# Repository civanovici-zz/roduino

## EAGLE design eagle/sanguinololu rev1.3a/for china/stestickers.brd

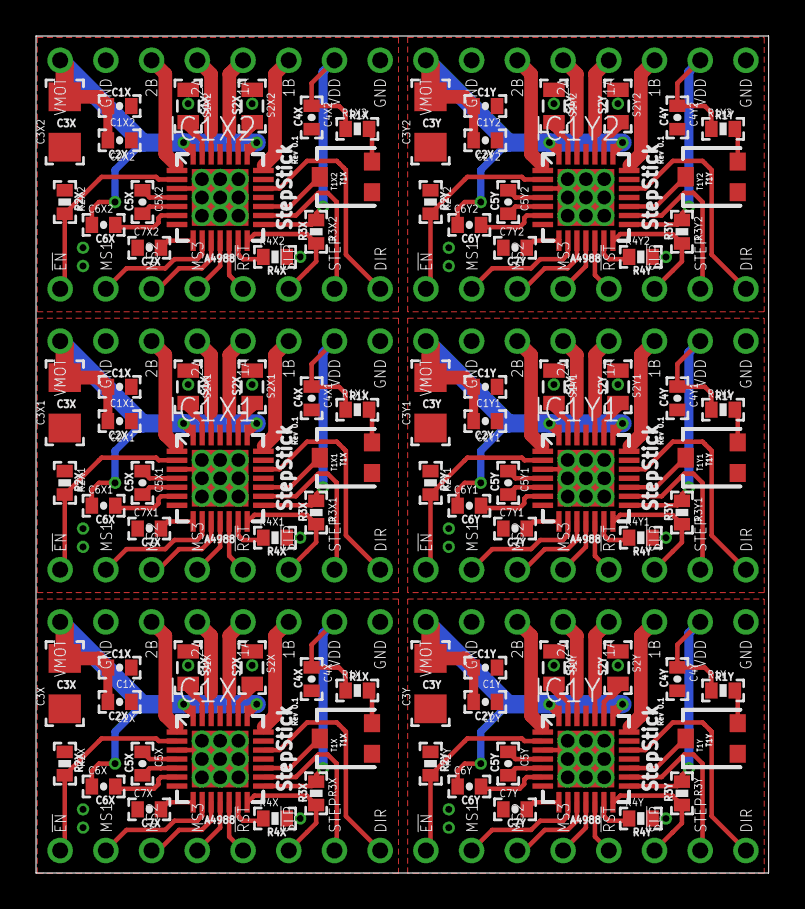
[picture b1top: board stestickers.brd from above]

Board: 2 copper layers, 40.7 x 46.5 mm, 96 parts (0 on the bottom side), 135 nets.

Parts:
C1X, C1X1, C1X2, C1Y, C1Y1, C1Y2, C2X, C2X1, C2X2, C2Y, C2Y1, C2Y2, C5X, C5X1, C5X2, C5Y, C5Y1, C5Y2, C6X, C6X1, C6X2, C6Y, C6Y1, C6Y2: .1uf; 0402-CAP
C3X, C3X1, C3X2, C3Y, C3Y1, C3Y2: 4.7uF; 1206
C4X, C4X1, C4X2, C4Y, C4Y1, C4Y2, C7X, C7X1, C7X2, C7Y, C7Y1, C7Y2: .22uf; 0402-CAP
IC1X, IC1X1, IC1X2, IC1Y, IC1Y1, IC1Y2: A4988; QFN28ET
J1X, J1X1, J1X2, J1Y, J1Y1, J1Y2: CLONOLU
R1X, R1X1, R1X2, R1Y, R1Y1, R1Y2: 20k; 0402-RES
R2X, R2X1, R2X2, R2Y, R2Y1, R2Y2, R3X, R3X1, R3X2, R3Y, R3Y1, R3Y2: 100k; 0402-RES
R4X, R4X1, R4X2, R4Y, R4Y1, R4Y2: 10k; 0402-RES
S1X, S1X1, S1X2, S1Y, S1Y1, S1Y2, S2X, S2X1, S2X2, S2Y, S2Y1, S2Y2: 0.2; 0805
T1X, T1X1, T1X2, T1Y, T1Y1, T1Y2: TRIM; TRIMPOT-3MM

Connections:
GND: C1X.1, C1Y.1, C2X.1, C2Y.1, C3X.1, C3Y.1, C4X.2, C4Y.2, C7X.1, C7Y.1, IC1X.3, IC1X.7, IC1X.18, IC1X.20, IC1X.25, IC1X.EXP, IC1Y.3, IC1Y.7, IC1Y.18, IC1Y.20, IC1Y.25, IC1Y.EXP, J1X.GND$1, J1X.GND$2, J1Y.GND$1, J1Y.GND$2, R2X.1, R2Y.1, R4X.2, R4Y.2, S1X.1, S1Y.1, S2X.1, S2Y.1, T1X.1, T1Y.1
GND1: C1X1.1, C1Y1.1, C2X1.1, C2Y1.1, C3X1.1, C3Y1.1, C4X1.2, C4Y1.2, C7X1.1, C7Y1.1, IC1X1.3, IC1X1.7, IC1X1.18, IC1X1.20, IC1X1.25, IC1X1.EXP, IC1Y1.3, IC1Y1.7, IC1Y1.18, IC1Y1.20, IC1Y1.25, IC1Y1.EXP, J1X1.GND$1, J1X1.GND$2, J1Y1.GND$1, J1Y1.GND$2, R2X1.1, R2Y1.1, R4X1.2, R4Y1.2, S1X1.1, S1Y1.1, S2X1.1, S2Y1.1, T1X1.1, T1Y1.1
GND2: C1X2.1, C1Y2.1, C2X2.1, C2Y2.1, C3X2.1, C3Y2.1, C4X2.2, C4Y2.2, C7X2.1, C7Y2.1, IC1X2.3, IC1X2.7, IC1X2.18, IC1X2.20, IC1X2.25, IC1X2.EXP, IC1Y2.3, IC1Y2.7, IC1Y2.18, IC1Y2.20, IC1Y2.25, IC1Y2.EXP, J1X2.GND$1, J1X2.GND$2, J1Y2.GND$1, J1Y2.GND$2, R2X2.1, R2Y2.1, R4X2.2, R4Y2.2, S1X2.1, S1Y2.1, S2X2.1, S2Y2.1, T1X2.1, T1Y2.1
VDD: C4X.1, C4Y.1, IC1X.15, IC1Y.15, J1X.VDD, J1Y.VDD, R1X.1, R1Y.1, R3X.1, R3Y.1
VDD1: C4X1.1, C4Y1.1, IC1X1.15, IC1Y1.15, J1X1.VDD, J1Y1.VDD, R1X1.1, R1Y1.1, R3X1.1, R3Y1.1
VDD2: C4X2.1, C4Y2.1, IC1X2.15, IC1Y2.15, J1X2.VDD, J1Y2.VDD, R1X2.1, R1Y2.1, R3X2.1, R3Y2.1
VMOT: C1X.2, C1Y.2, C2X.2, C2Y.2, C3X.2, C3Y.2, C6X.1, C6Y.1, IC1X.22, IC1X.28, IC1Y.22, IC1Y.28, J1X.VMOT, J1Y.VMOT
VMOT1: C1X1.2, C1Y1.2, C2X1.2, C2Y1.2, C3X1.2, C3Y1.2, C6X1.1, C6Y1.1, IC1X1.22, IC1X1.28, IC1Y1.22, IC1Y1.28, J1X1.VMOT, J1Y1.VMOT
VMOT2: C1X2.2, C1Y2.2, C2X2.2, C2Y2.2, C3X2.2, C3Y2.2, C6X2.1, C6Y2.1, IC1X2.22, IC1X2.28, IC1Y2.22, IC1Y2.28, J1X2.VMOT, J1Y2.VMOT
XCP1: C5X.1, IC1X.4
XCP2: C5X.2, IC1X.5
XCP3: C5X1.1, IC1X1.4
XCP4: C5X1.2, IC1X1.5
XCP5: C5X2.1, IC1X2.4
XCP6: C5X2.2, IC1X2.5
XDIR: IC1X.19, J1X.DIR
XDIR1: IC1X1.19, J1X1.DIR
XDIR2: IC1X2.19, J1X2.DIR
XENABLE: IC1X.2, J1X.!EN, R2X.2
XENABLE1: IC1X1.2, J1X1.!EN, R2X1.2
XENABLE2: IC1X2.2, J1X2.!EN, R2X2.2
XMS1: IC1X.9, J1X.MS1
XMS2: IC1X.10, J1X.MS2
XMS3: IC1X.11, J1X.MS3
XMS4: IC1X1.9, J1X1.MS1
XMS5: IC1X1.10, J1X1.MS2
XMS6: IC1X1.11, J1X1.MS3
XMS7: IC1X2.9, J1X2.MS1
XMS8: IC1X2.10, J1X2.MS2
XMS9: IC1X2.11, J1X2.MS3
XOUT1A: IC1X.24, J1X.1A
XOUT1A1: IC1X1.24, J1X1.1A
XOUT1A2: IC1X2.24, J1X2.1A
XOUT1B: IC1X.21, J1X.1B
XOUT1B1: IC1X1.21, J1X1.1B
XOUT1B2: IC1X2.21, J1X2.1B
XOUT2A: IC1X.26, J1X.2A
XOUT2A1: IC1X1.26, J1X1.2A
XOUT2A2: IC1X2.26, J1X2.2A
XOUT2B: IC1X.1, J1X.2B
XOUT2B1: IC1Y.1, J1Y.2B
XOUT2B2: IC1X1.1, J1X1.2B
XOUT2B3: IC1Y1.1, J1Y1.2B
XOUT2B4: IC1X2.1, J1X2.2B
XOUT2B5: IC1Y2.1, J1Y2.2B
XREF: IC1X.17, T1X.2
XREF1: IC1X1.17, T1X1.2
XREF2: R1X.2, T1X.3
XREF3: R1X1.2, T1X1.3
XREF4: IC1X2.17, T1X2.2
XREF5: R1X2.2, T1X2.3
XRESET: IC1X.12, J1X.!RST
XRESET1: IC1X1.12, J1X1.!RST
XRESET2: IC1X2.12, J1X2.!RST
XROSC: IC1X.13, R4X.1
XROSC1: IC1X1.13, R4X1.1
XROSC2: IC1X2.13, R4X2.1
XSENSE1: IC1X.23, S2X.2
XSENSE2: IC1X.27, S1X.2
XSENSE3: IC1X1.27, S1X1.2
XSENSE4: IC1X1.23, S2X1.2
XSENSE5: IC1X2.27, S1X2.2
XSENSE6: IC1X2.23, S2X2.2
XSLEEP: IC1X.14, J1X.!SLP, R3X.2
XSLEEP1: IC1X1.14, J1X1.!SLP, R3X1.2
XSLEEP2: IC1X2.14, J1X2.!SLP, R3X2.2
XSTEP: IC1X.16, J1X.STEP
XSTEP1: IC1X1.16, J1X1.STEP
XSTEP2: IC1X2.16, J1X2.STEP
XVCP: C6X.2, IC1X.6
XVCP1: C6X1.2, IC1X1.6
XVCP2: C6X2.2, IC1X2.6
XVREG: C7X.2, IC1X.8
XVREG1: C7X1.2, IC1X1.8
XVREG2: C7X2.2, IC1X2.8
YCP1: C5Y.1, IC1Y.4
YCP2: C5Y.2, IC1Y.5
YCP3: C5Y1.1, IC1Y1.4
YCP4: C5Y1.2, IC1Y1.5
YCP5: C5Y2.1, IC1Y2.4
YCP6: C5Y2.2, IC1Y2.5
YDIR1: IC1Y.19, J1Y.DIR
YDIR2: IC1Y1.19, J1Y1.DIR
YDIR3: IC1Y2.19, J1Y2.DIR
YENABLE: IC1Y.2, J1Y.!EN, R2Y.2
YENABLE1: IC1Y1.2, J1Y1.!EN, R2Y1.2
YENABLE2: IC1Y2.2, J1Y2.!EN, R2Y2.2
YMS1: IC1Y.9, J1Y.MS1
YMS2: IC1Y.10, J1Y.MS2
YMS3: IC1Y.11, J1Y.MS3
YMS4: IC1Y1.9, J1Y1.MS1
YMS5: IC1Y1.10, J1Y1.MS2
YMS6: IC1Y1.11, J1Y1.MS3
YMS7: IC1Y2.9, J1Y2.MS1
YMS8: IC1Y2.10, J1Y2.MS2
YMS9: IC1Y2.11, J1Y2.MS3
YOUT1A: IC1Y.24, J1Y.1A
YOUT1A1: IC1Y1.24, J1Y1.1A
YOUT1A2: IC1Y2.24, J1Y2.1A
YOUT1B: IC1Y.21, J1Y.1B
YOUT1B1: IC1Y1.21, J1Y1.1B
YOUT1B2: IC1Y2.21, J1Y2.1B
YOUT2A: IC1Y.26, J1Y.2A
YOUT2A1: IC1Y1.26, J1Y1.2A
YOUT2A2: IC1Y2.26, J1Y2.2A
YREF: IC1Y.17, T1Y.2
YREF1: R1Y.2, T1Y.3
YREF2: IC1Y1.17, T1Y1.2
YREF3: R1Y1.2, T1Y1.3
YREF4: IC1Y2.17, T1Y2.2
YREF5: R1Y2.2, T1Y2.3
YRESET: IC1Y.12, J1Y.!RST
YRESET1: IC1Y1.12, J1Y1.!RST
YRESET2: IC1Y2.12, J1Y2.!RST
YROSC: IC1Y.13, R4Y.1
YROSC1: IC1Y1.13, R4Y1.1
YROSC2: IC1Y2.13, R4Y2.1
YSENSE1: IC1Y.23, S2Y.2
YSENSE2: IC1Y.27, S1Y.2
YSENSE3: IC1Y1.27, S1Y1.2
YSENSE4: IC1Y1.23, S2Y1.2
YSENSE5: IC1Y2.27, S1Y2.2
YSENSE6: IC1Y2.23, S2Y2.2
YSLEEP: IC1Y.14, J1Y.!SLP, R3Y.2
YSLEEP1: IC1Y1.14, J1Y1.!SLP, R3Y1.2
YSLEEP2: IC1Y2.14, J1Y2.!SLP, R3Y2.2
YSTEP: IC1Y.16, J1Y.STEP
YSTEP1: IC1Y1.16, J1Y1.STEP
YSTEP2: IC1Y2.16, J1Y2.STEP
YVCP: C6Y.2, IC1Y.6
YVCP1: C6Y1.2, IC1Y1.6
YVCP2: C6Y2.2, IC1Y2.6
YVREG: C7Y.2, IC1Y.8
YVREG1: C7Y1.2, IC1Y1.8
YVREG2: C7Y2.2, IC1Y2.8

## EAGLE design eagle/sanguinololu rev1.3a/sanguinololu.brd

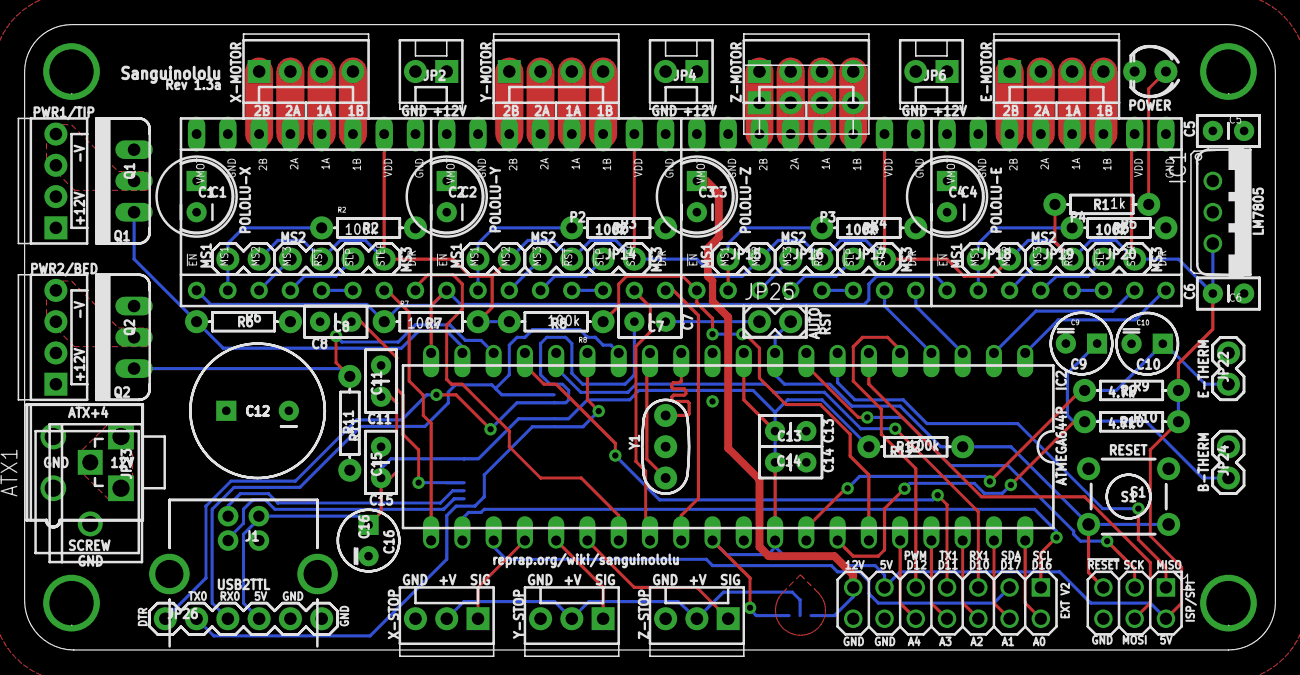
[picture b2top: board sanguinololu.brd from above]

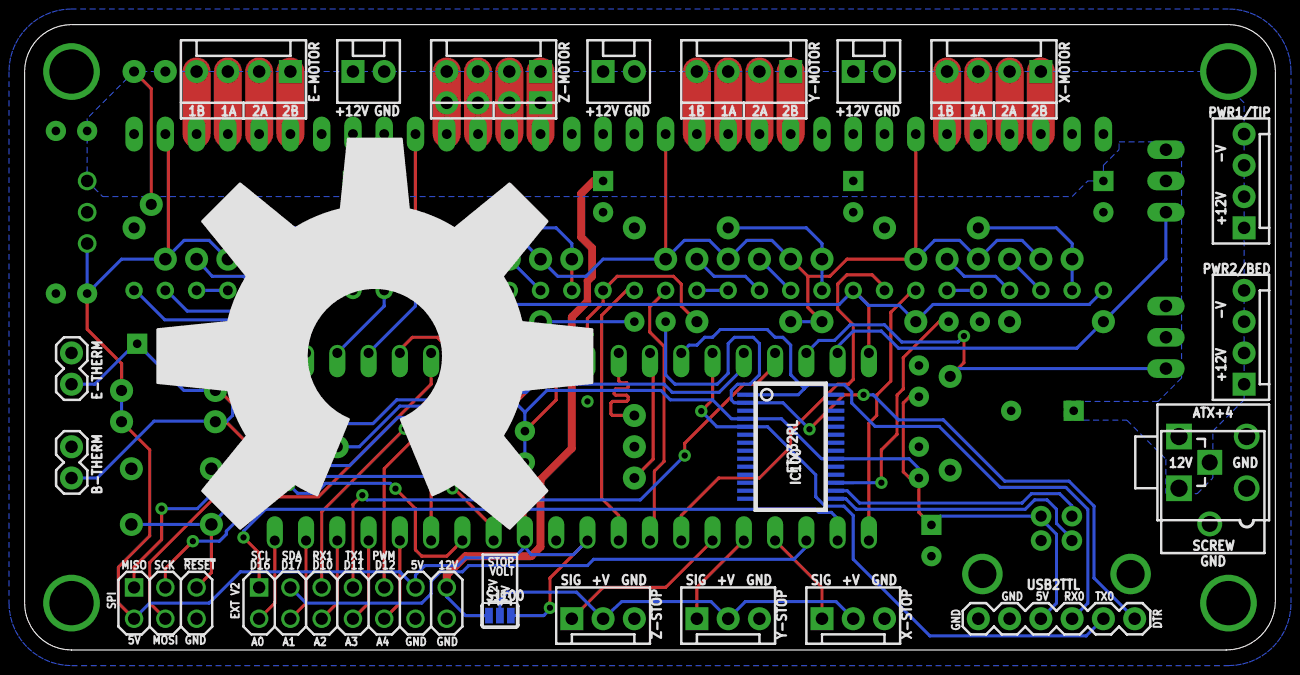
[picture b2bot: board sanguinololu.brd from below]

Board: 2 copper layers, 101.6 x 50.8 mm, 77 parts (2 on the bottom side), 79 nets.

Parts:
ATX1: ATX-4VERTICAL; MINIFITJR-4-VERTICAL
C1, C2, C3, C4: 100uf; CPOL-RADIAL-100UF-25V
C5: 0.33uF; CAP-PTH-SMALL2
C6, C7, C8, C11, C13, C14, C15: 0.1uF; CAP-PTH-SMALL2
C9, C10: 10uF; CPOL-RADIAL-10UF-25V
C12: 1000uF; CPOL-RADIAL-1000UF-25V
C16: 4.7uF; CPOL-RADIAL-10UF-25V
IC1: LM7805; 78XXL-CUSTOM
IC2: ATMEGA644-20PU; DIL40
IC100: FT232RL; SSOP28DB
J1: USB; USB-B-PTH
JP1: MOT-X; MOLEX-1X4
JP2, JP4, JP6: 12VPWR; MOLEX-1X2
JP3: MOT-Y; MOLEX-1X4
JP5, JP30: MOT-Z; MOLEX-1X4
JP7: MOT-E; MOLEX-1X4
JP8: HOTEND; MOLEX-1X4
JP9: X-MS1; 1X02
JP10: X-MS2; 1X02
JP11: X-MS3; 1X02
JP12: Y-MS1; 1X02
JP13: Y-MS2; 1X02
JP14: Y-MS3; 1X02
JP15: Z-MS1; 1X02
JP16: Z-MS2; 1X02
JP17: Z-MS3; 1X02
JP18: E-MS1; 1X02
JP19: E-MS2; 1X02
JP20: E-MS3; 1X02
JP21: HOTBED; MOLEX-1X4
JP22: E-THERM; 1X02
JP23: SCREW; SCREWTERMINAL-5MM-2
JP24: B-THERM; 1X02
JP25: AUTO RESET; 1X02
JP26: USB2TTL; 1X06
JP27: X-STOP; MOLEX-1X3
JP28: Y-STOP; MOLEX-1X3
JP29: Z-STOP; MOLEX-1X3
LED1: POWER; LED3MM
P1: POLOLU-X; POLOLU-ALLEGRO-PTH
P2: POLOLU-Y; POLOLU-ALLEGRO-PTH
P3: POLOLU-Z; POLOLU-ALLEGRO-PTH
P4: POLOLU-E; POLOLU-ALLEGRO-PTH
Q1, Q2: RFP30N06LE; TO220V
R1: 1k; AXIAL-0.3
R2, R3, R4, R5, R7, R8, R12: 100k; AXIAL-0.3
R6, R11: 10k; AXIAL-0.3
R9, R10: 4.7k; AXIAL-0.3
S1: RESET; TACTILE-PTH
SJ100: 5v/12v; SJ_3
U$17, U$37, U$38: PLATED-SCREW; PLATEDSCREW
U$24: IO_HEADERS_SCREW; IO_HEADER-PLATEDSCREW
Y1: 16MHz 22pF; RESONATOR-PTH

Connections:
3V3: C8.1, IC100.17
5V: C6.1, C11.1, C13.2, C14.1, C15.1, C16.1, IC1.OUT, IC2.10, IC2.30, IC2.32, IC100.4, IC100.20, J1.VBUS, JP9.2, JP10.2, JP11.2, JP12.2, JP13.2, JP14.2, JP15.2, JP16.2, JP17.2, JP18.2, JP19.2, JP20.2, JP26.4, P1.VDD, P2.VDD, P3.VDD, P4.VDD, R1.P$2, R7.P$2, R8.P$2, R9.P$2, R10.P$2, R12.P$2, SJ100.3, U$24.5V, U$24.5V1
12V: ATX1.3, ATX1.4, C1.1, C2.1, C3.1, C4.1, C5.1, C12.1, IC1.IN, JP2.1, JP4.1, JP6.1, JP8.1, JP8.2, JP21.1, JP21.2, JP23.1, P1.VMOT, P2.VMOT, P3.VMOT, P4.VMOT, SJ100.1, U$24.12V
!FTDI-RESET: C7.1, JP25.1
!HOTBED: IC2.18, Q2.1, R11.P$1
!HOTEND: IC2.19, Q1.1, R6.P$1
!RESET: IC2.9, JP25.2, R12.P$1, S1.3, S1.4, U$24.RST
!STEP-ENABLE: IC2.20, P1.!EN, P2.!EN, P4.!EN, R7.P$1
!STEP-ENABLE-Z: IC2.35, P3.!EN, R8.P$1
#DTR: C7.2, IC100.2, JP26.1
A0: IC2.40, U$24.A0
A1: IC2.39, U$24.A1
A2: IC2.38, U$24.A2
A3: IC2.37, U$24.A3
A4: IC2.36, U$24.A4
AIFO: IC2.14, IC100.1, JP26.3
AOFI: IC2.15, IC100.5, JP26.2
B-THERM: C9.1, IC2.34, JP24.1, R10.P$1
E-DIR: IC2.1, P4.DIR
E-MOT-1A: JP7.3, P4.1A
E-MOT-1B: JP7.4, P4.1B
E-MOT-2A: JP7.2, P4.2A
E-MOT-2B: JP7.1, P4.2B
E-MS1: JP18.1, P4.MS1, R5.P$1
E-MS2: JP19.1, P4.MS2
E-MS3: JP20.1, P4.MS3
E-RESETSLEEP: P4.!RST, P4.!SLP
E-STEP: IC2.2, P4.STEP
E-THERM: C10.1, IC2.33, JP22.1, R9.P$1
ENDSTOP+V: JP27.2, JP28.2, JP29.2, SJ100.2
GND: ATX1.1, ATX1.2, C1.2, C2.2, C3.2, C4.2, C5.2, C6.2, C8.2, C9.2, C10.2, C11.2, C12.2, C13.1, C14.2, C15.2, C16.2, IC1.GND, IC2.11, IC2.31, IC100.7, IC100.18, IC100.21, IC100.25, IC100.26, J1.GND, J1.P$1, J1.P$2, JP2.2, JP4.2, JP6.2, JP22.2, JP23.2, JP24.2, JP26.5, JP26.6, JP27.3, JP28.3, JP29.3, LED1.K, P1.GNDMOT, P1.GNDVDD, P2.GNDMOT, P2.GNDVDD, P3.GNDMOT, P3.GNDVDD, P4.GNDMOT, P4.GNDVDD, Q1.3, Q2.3, R2.P$2, R3.P$2, R4.P$2, R5.P$2, R6.P$2, R11.P$2, S1.1, S1.2, U$17.GND, U$24.GND, U$24.GND1, U$24.GND2, U$24.GNDSCREW, U$37.GND, U$38.GND, Y1.2
HOTBED-GND: JP21.3, JP21.4, Q2.2
HOTEND-GND: JP8.3, JP8.4, Q1.2
LED1: LED1.A, R1.P$1
PB4-PWM: IC2.5, U$24.PWM
PB5-MOSI: IC2.6, U$24.MOSI
PB6-MISO: IC2.7, U$24.MISO
PB7-SCK: IC2.8, U$24.SCK
PC0-SCL: IC2.22, U$24.SCL
PC1-SDA: IC2.23, U$24.SDA
PD2-RX1: IC2.16, U$24.RX1
PD3-TX1: IC2.17, U$24.TX1
USBDM: IC100.16, J1.D-
USBDP: IC100.15, J1.D+
X-DIR: IC2.27, P1.DIR
X-MOT-1A: JP1.3, P1.1A
X-MOT-1B: JP1.4, P1.1B
X-MOT-2A: JP1.2, P1.2A
X-MOT-2B: JP1.1, P1.2B
X-MS1: JP9.1, P1.MS1, R2.P$1
X-MS2: JP10.1, P1.MS2
X-MS3: JP11.1, P1.MS3
X-RESETSLEEP: P1.!RST, P1.!SLP
X-STEP: IC2.21, P1.STEP
X-STOP: IC2.24, JP27.1
XTAL1: IC2.13, Y1.3
XTAL2: IC2.12, Y1.1
Y-DIR: IC2.29, P2.DIR
Y-MOT-1A: JP3.3, P2.1A
Y-MOT-1B: JP3.4, P2.1B
Y-MOT-2A: JP3.2, P2.2A
Y-MOT-2B: JP3.1, P2.2B
Y-MS1: JP12.1, P2.MS1, R3.P$1
Y-MS2: JP13.1, P2.MS2
Y-MS3: JP14.1, P2.MS3
Y-RESETSLEEP: P2.!RST, P2.!SLP
Y-STEP: IC2.28, P2.STEP
Y-STOP: IC2.25, JP28.1
Z-DIR: IC2.3, P3.DIR
Z-MOT-1A: JP5.3, JP30.3, P3.1A
Z-MOT-1B: JP5.4, JP30.4, P3.1B
Z-MOT-2A: JP5.2, JP30.2, P3.2A
Z-MOT-2B: JP5.1, JP30.1, P3.2B
Z-MS1: JP15.1, P3.MS1, R4.P$1
Z-MS2: JP16.1, P3.MS2
Z-MS3: JP17.1, P3.MS3
Z-RESETSLEEP: P3.!RST, P3.!SLP
Z-STEP: IC2.4, P3.STEP
Z-STOP: IC2.26, JP29.1

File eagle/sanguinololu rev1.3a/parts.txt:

-----------FTDI-----------,
C7,       0.1uF,            CAPPTH2                   CAP-PTH-SMALL2         
C8,       0.1uF,            CAPPTH2                   CAP-PTH-SMALL2         
C11,      0.1uF,            CAPPTH2                   CAP-PTH-SMALL2         
C15,      0.1uF,            CAPPTH2                   CAP-PTH-SMALL2         
C16,      4.7uF,            CAP_POLPTH2               CPOL-RADIAL-10UF-25V   
IC100,    FT232RL,          FT232RLSSOP               SSOP28DB               
J1,       USB,              USBPTH                    USB-B-PTH              


-----------VREG-----------,
IC1,       LM7805,          VREG-NOGND                VREG-NOGND             vreg
C5,       0.33uF,           CAPPTH2                   CAP-PTH-SMALL2         
C6,       0.1uF,            CAPPTH2                   CAP-PTH-SMALL2         
JP23,     SCREW,            M025MM                    SCREWTERMINAL-5MM-2    


-----------ATX------------,
ATX1,     ATX-4VERTICAL,    ATX-4VERTICAL             MINIFITJR-4-VERTICAL   atx-power-supply
HDDPWR,   5v/12v,           DRIVEPWRVERTICAL          HDD-VERTICAL           atx-power-supply


-----------CORE-----------,
IC2,      ATMEGA644-20PU,   ATMEGA644-20PU            DIL40                  atmel
DIP-40,   SOCKET,
SHUNT,    MS, QTY12
MALE PIN,  QTY70 (10x7)
FEMALE PIN HEADER, 16pin, qty4


LED1,     POWER,            LED3MM                    LED3MM                 
Y1,       16MHz 22pF,       RESONATORPTH              RESONATOR-PTH          
S1,       RESET,            TAC_SWITCHPTH             TACTILE-PTH            
Q1,       RFP30N06LE,       MOSFET-NCHANNELPTH2       TO220V                 
Q2,       RFP30N06LE,       MOSFET-NCHANNELPTH2       TO220V                 

C1,       100uf,            CAP_POLPTH1               CPOL-RADIAL-100UF-35V  
C2,       100uf,            CAP_POLPTH1               CPOL-RADIAL-100UF-35V  
C3,       100uf,            CAP_POLPTH1               CPOL-RADIAL-100UF-35V  
C4,       100uf,            CAP_POLPTH1               CPOL-RADIAL-100UF-35V  
C9,       10uF,             CAP_POLPTH2               CPOL-RADIAL-10UF-35V   
C10,      10uF,             CAP_POLPTH2               CPOL-RADIAL-10UF-35V   
C12,      1000uF,           CAP_POLPTH4               CPOL-RADIAL-1000UF-35V 
C14,      0.1uF,            CAPPTH2                   CAP-PTH-SMALL2         
C13,      0.1uF,            CAPPTH2                   CAP-PTH-SMALL2         

R1,       1k,               RESISTORPTH1              AXIAL-0.3              
R2,       100k,             RESISTORPTH1              AXIAL-0.3              
R3,       100k,             RESISTORPTH1              AXIAL-0.3              
R4,       100k,             RESISTORPTH1              AXIAL-0.3              
R5,       100k,             RESISTORPTH1              AXIAL-0.3              
R6,       10k,              RESISTORPTH1              AXIAL-0.3              
R7,       100k,             RESISTORPTH1              AXIAL-0.3              
R8,       100k,             RESISTORPTH1              AXIAL-0.3              
R9,       4.7k,             RESISTORPTH1              AXIAL-0.3              
R10,      4.7k,             RESISTORPTH1              AXIAL-0.3              
R11,      10k,              RESISTORPTH1              AXIAL-0.3              
R12,      100k,             RESISTORPTH1              AXIAL-0.3

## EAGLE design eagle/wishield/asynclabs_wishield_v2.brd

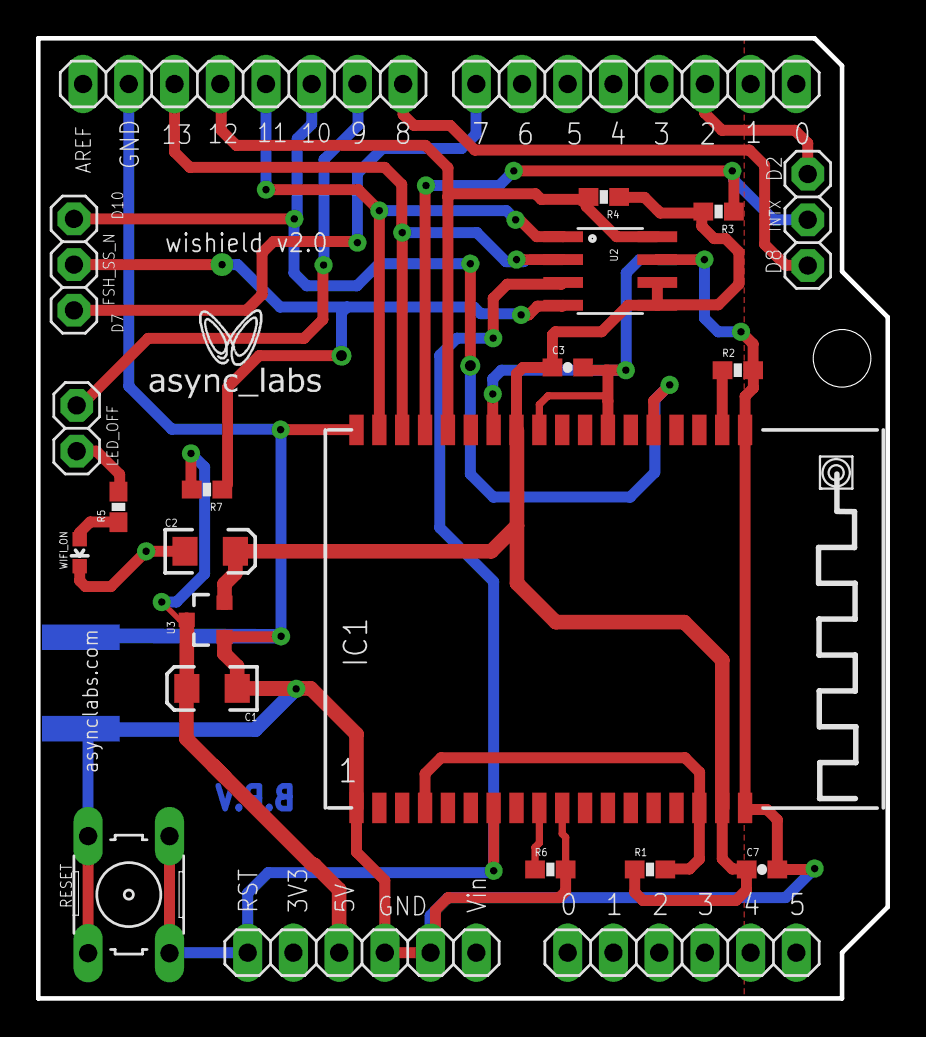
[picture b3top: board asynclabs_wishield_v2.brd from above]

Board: 2 copper layers, 47.2 x 53.3 mm, 23 parts (0 on the bottom side), 19 nets.

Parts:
C1, C2: 10uF; EIA3216
C3, C7: 100nF; 0603-CAP
IC1: 802.11; ZG2100MOD
INTX: PINHD3
JP3: PINHD2
JP4: PINHD3
R1, R2, R3, R4, R6, R7: 4.7k; 0603-RES
R5: 330; 0603-RES
RESET: SWITCH
U2: SO08
U3: MCP1700_SOT23; SOT23-3
U$1: POWER; 1X06
U$2: ANALOG; 1X06
U$3: DIGITAL_0_7; 1X08
U$4: DIGITAL_8_13; 1X08
WIFI_ON: red; LED-0603

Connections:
+3V3: C2.A, C3.1, C7.1, IC1.VDD33_17, IC1.VDD33_29, R1.1, R3.2, R4.1, U2.5, U2.6, U3.2
+5V: C1.A, R7.2, U3.3, U$1.3
CE_N: IC1.CE_N, R2.1
D2: INTX.3, U$3.6
D7: JP4.3, U$3.1
D8: INTX.1, U$4.8
DIG9: JP3.1, U$4.7
FLASH_SS_N: JP4.2, R7.1, U2.4
GND: C1.C, C2.C, C3.2, C7.2, IC1.GND1, IC1.GND10, IC1.GND18, IC1.GND19, IC1.GND25, IC1.GND28, IC1.GND30, IC1.GND36, R2.2, R6.2, RESET.3, RESET.4, U2.7, U3.1, U$1.4, U$1.5, U$4.2, WIFI_ON.C
INTX: IC1.INTX, INTX.2, R3.1
JRST: IC1.JRST, R6.1
unnamed: JP3.2, R5.2
unnamed: R5.1, WIFI_ON.A
RST: IC1.RESETN, RESET.1, RESET.2, U2.3, U$1.1
SCK: IC1.SCK, U2.2, U$4.3
SDI: IC1.SDI, U2.1, U$4.5
SDO: IC1.SDO, R4.2, U2.8, U$4.4
SS_N: IC1.SS_N, JP4.1, U$4.6
VDD_TIE: IC1.GND16, IC1.TCK, R1.2

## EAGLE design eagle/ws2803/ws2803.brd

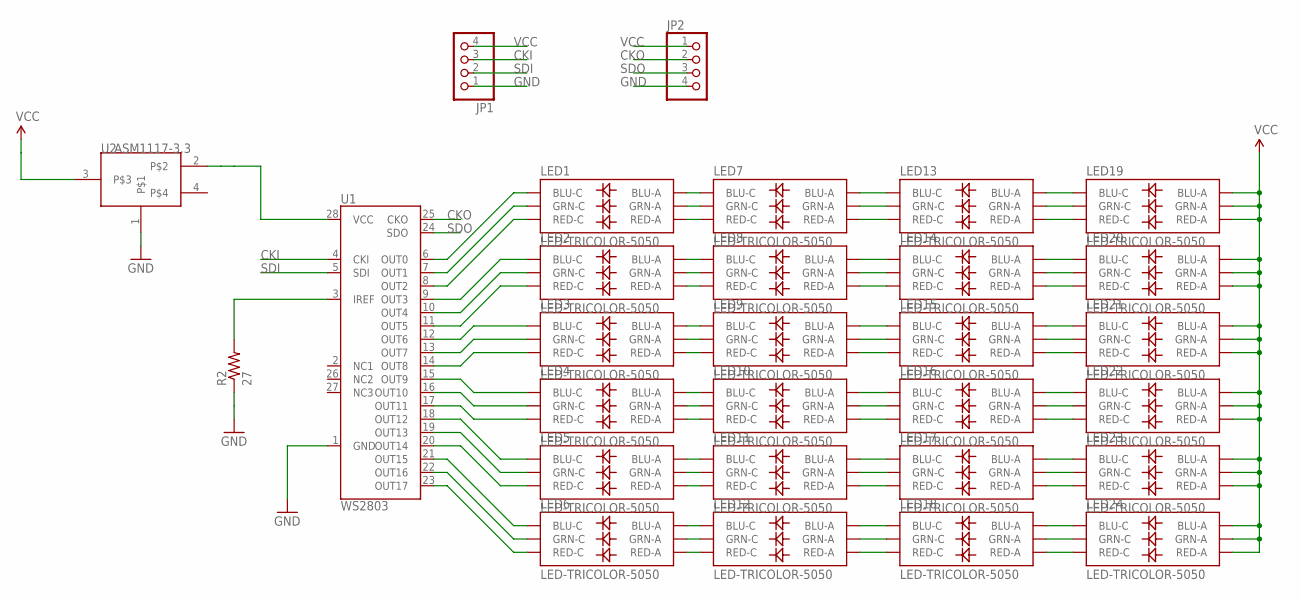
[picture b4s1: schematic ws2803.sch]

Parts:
JP1, JP2: PINHD-1X4; 1X04
LED1, LED2, LED3, LED4, LED5, LED6, LED7, LED8, LED9, LED10, LED11, LED12, LED13, LED14, LED15, LED16, LED17, LED18, LED19, LED20, LED21, LED22, LED23, LED24: LED-TRICOLOR-5050
R2: 27; 0603-RES
U1: WS2803; SOP-28
U2: ASM1117-3.3; SOT223

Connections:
CKI: JP1.3, U1.4 (CKI)
CKO: JP2.2, U1.25 (CKO)
GND: JP1.1, JP2.4, R2.1, U1.1 (GND), U2.1
unnamed: LED3.4 (BLU-C), U1.12 (OUT6)
unnamed: LED3.6 (GRN-C), U1.13 (OUT7)
unnamed: LED3.5 (RED-C), U1.14 (OUT8)
unnamed: R2.2, U1.3 (IREF)
unnamed: LED4.4 (BLU-C), U1.15 (OUT9)
unnamed: LED4.6 (GRN-C), U1.16 (OUT10)
unnamed: LED4.5 (RED-C), U1.17 (OUT11)
unnamed: LED5.4 (BLU-C), U1.18 (OUT12)
unnamed: LED5.6 (GRN-C), U1.19 (OUT13)
unnamed: LED5.5 (RED-C), U1.20 (OUT14)
unnamed: LED6.4 (BLU-C), U1.21 (OUT15)
unnamed: LED6.6 (GRN-C), U1.22 (OUT16)
unnamed: LED6.5 (RED-C), U1.23 (OUT17)
unnamed: LED2.5 (RED-C), U1.11 (OUT5)
unnamed: LED2.6 (GRN-C), U1.10 (OUT4)
unnamed: LED2.4 (BLU-C), U1.9 (OUT3)
unnamed: LED1.5 (RED-C), U1.8 (OUT2)
unnamed: LED1.6 (GRN-C), U1.7 (OUT1)
unnamed: LED1.4 (BLU-C), U1.6 (OUT0)
unnamed: LED1.3 (BLU-A), LED7.4 (BLU-C)
unnamed: LED1.1 (GRN-A), LED7.6 (GRN-C)
unnamed: LED1.2 (RED-A), LED7.5 (RED-C)
unnamed: LED2.3 (BLU-A), LED8.4 (BLU-C)
unnamed: LED2.1 (GRN-A), LED8.6 (GRN-C)
unnamed: LED2.2 (RED-A), LED8.5 (RED-C)
unnamed: LED3.3 (BLU-A), LED9.4 (BLU-C)
unnamed: LED3.1 (GRN-A), LED9.6 (GRN-C)
unnamed: LED3.2 (RED-A), LED9.5 (RED-C)
unnamed: LED4.3 (BLU-A), LED10.4 (BLU-C)
unnamed: LED4.1 (GRN-A), LED10.6 (GRN-C)
unnamed: LED4.2 (RED-A), LED10.5 (RED-C)
unnamed: LED5.3 (BLU-A), LED11.4 (BLU-C)
unnamed: LED5.1 (GRN-A), LED11.6 (GRN-C)
unnamed: LED5.2 (RED-A), LED11.5 (RED-C)
unnamed: LED6.3 (BLU-A), LED12.4 (BLU-C)
unnamed: LED6.1 (GRN-A), LED12.6 (GRN-C)
unnamed: LED6.2 (RED-A), LED12.5 (RED-C)
unnamed: LED12.3 (BLU-A), LED18.4 (BLU-C)
unnamed: LED7.1 (GRN-A), LED13.6 (GRN-C)
unnamed: LED7.2 (RED-A), LED13.5 (RED-C)
unnamed: LED7.3 (BLU-A), LED13.4 (BLU-C)
unnamed: LED8.3 (BLU-A), LED14.4 (BLU-C)
unnamed: LED8.1 (GRN-A), LED14.6 (GRN-C)
unnamed: LED8.2 (RED-A), LED14.5 (RED-C)
unnamed: LED9.3 (BLU-A), LED15.4 (BLU-C)
unnamed: LED9.1 (GRN-A), LED15.6 (GRN-C)
unnamed: LED9.2 (RED-A), LED15.5 (RED-C)
unnamed: LED10.3 (BLU-A), LED16.4 (BLU-C)
unnamed: LED10.1 (GRN-A), LED16.6 (GRN-C)
unnamed: LED10.2 (RED-A), LED16.5 (RED-C)
unnamed: LED11.3 (BLU-A), LED17.4 (BLU-C)
unnamed: LED11.1 (GRN-A), LED17.6 (GRN-C)
unnamed: LED11.2 (RED-A), LED17.5 (RED-C)
unnamed: LED12.2 (RED-A), LED18.5 (RED-C)
unnamed: LED12.1 (GRN-A), LED18.6 (GRN-C)
unnamed: LED18.1 (GRN-A), LED24.6 (GRN-C)
unnamed: LED13.3 (BLU-A), LED19.4 (BLU-C)
unnamed: LED13.1 (GRN-A), LED19.6 (GRN-C)
unnamed: LED13.2 (RED-A), LED19.5 (RED-C)
unnamed: LED14.3 (BLU-A), LED20.4 (BLU-C)
unnamed: LED14.1 (GRN-A), LED20.6 (GRN-C)
unnamed: LED14.2 (RED-A), LED20.5 (RED-C)
unnamed: LED15.3 (BLU-A), LED21.4 (BLU-C)
unnamed: LED15.1 (GRN-A), LED21.6 (GRN-C)
unnamed: LED15.2 (RED-A), LED21.5 (RED-C)
unnamed: LED16.3 (BLU-A), LED22.4 (BLU-C)
unnamed: LED16.1 (GRN-A), LED22.6 (GRN-C)
unnamed: LED16.2 (RED-A), LED22.5 (RED-C)
unnamed: LED17.3 (BLU-A), LED23.4 (BLU-C)
unnamed: LED17.1 (GRN-A), LED23.6 (GRN-C)
unnamed: LED17.2 (RED-A), LED23.5 (RED-C)
unnamed: LED18.3 (BLU-A), LED24.4 (BLU-C)
unnamed: LED18.2 (RED-A), LED24.5 (RED-C)
SDI: JP1.2, U1.5 (SDI)
SDO: JP2.3, U1.24 (SDO)
VCC: JP1.4, JP2.1, LED19.1 (GRN-A), LED19.2 (RED-A), LED19.3 (BLU-A), LED20.1 (GRN-A), LED20.2 (RED-A), LED20.3 (BLU-A), LED21.1 (GRN-A), LED21.2 (RED-A), LED21.3 (BLU-A), LED22.1 (GRN-A), LED22.2 (RED-A), LED22.3 (BLU-A), LED23.1 (GRN-A), LED23.2 (RED-A), LED23.3 (BLU-A), LED24.1 (GRN-A), LED24.2 (RED-A), LED24.3 (BLU-A), U2.3
VCC1: U1.28 (VCC), U2.2

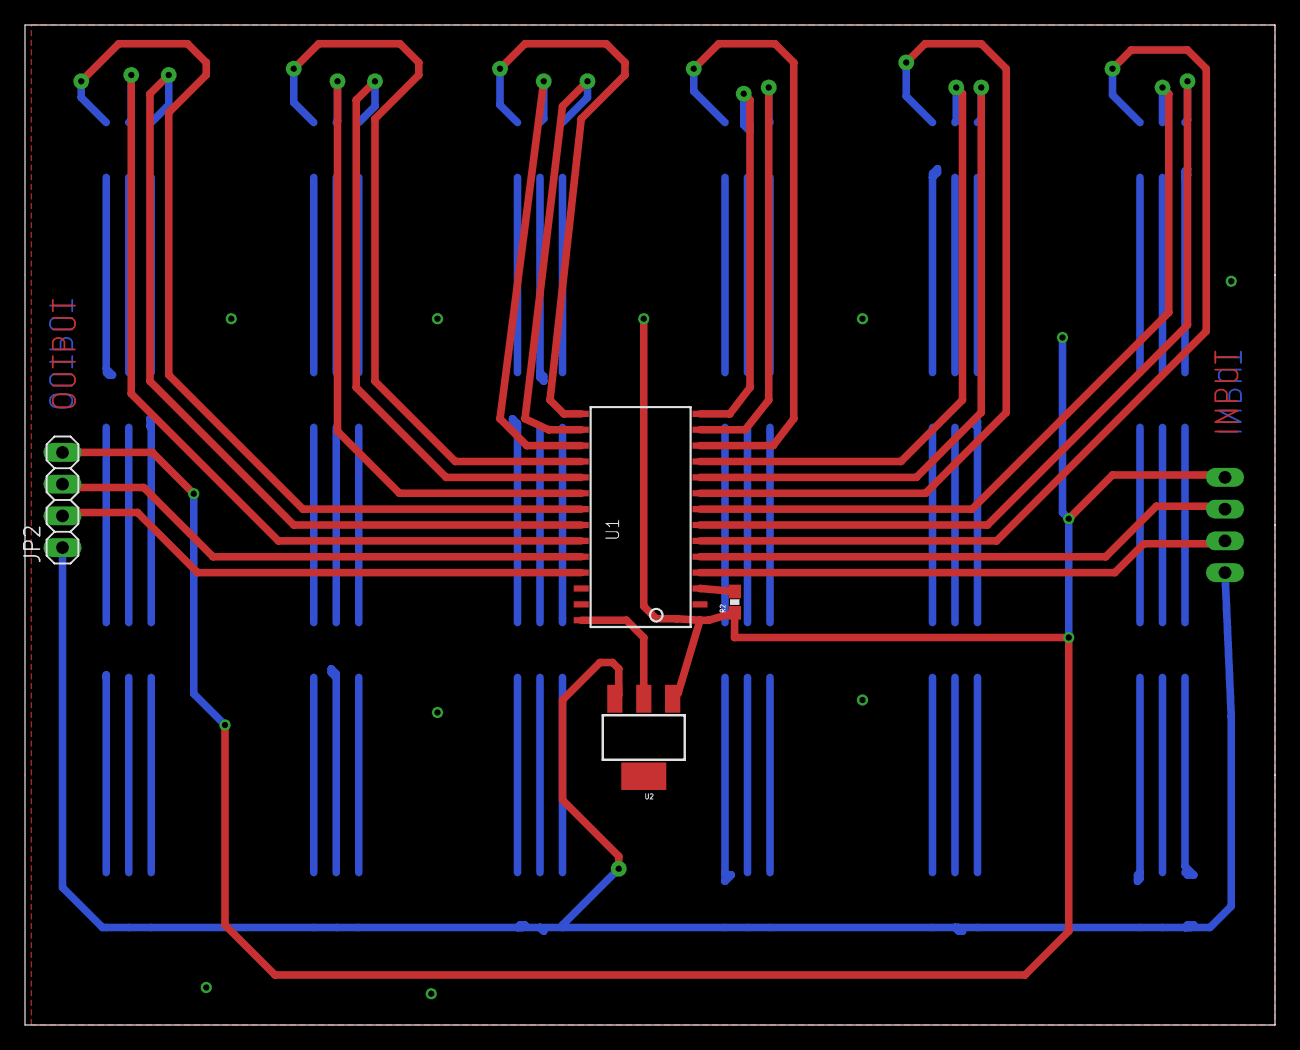
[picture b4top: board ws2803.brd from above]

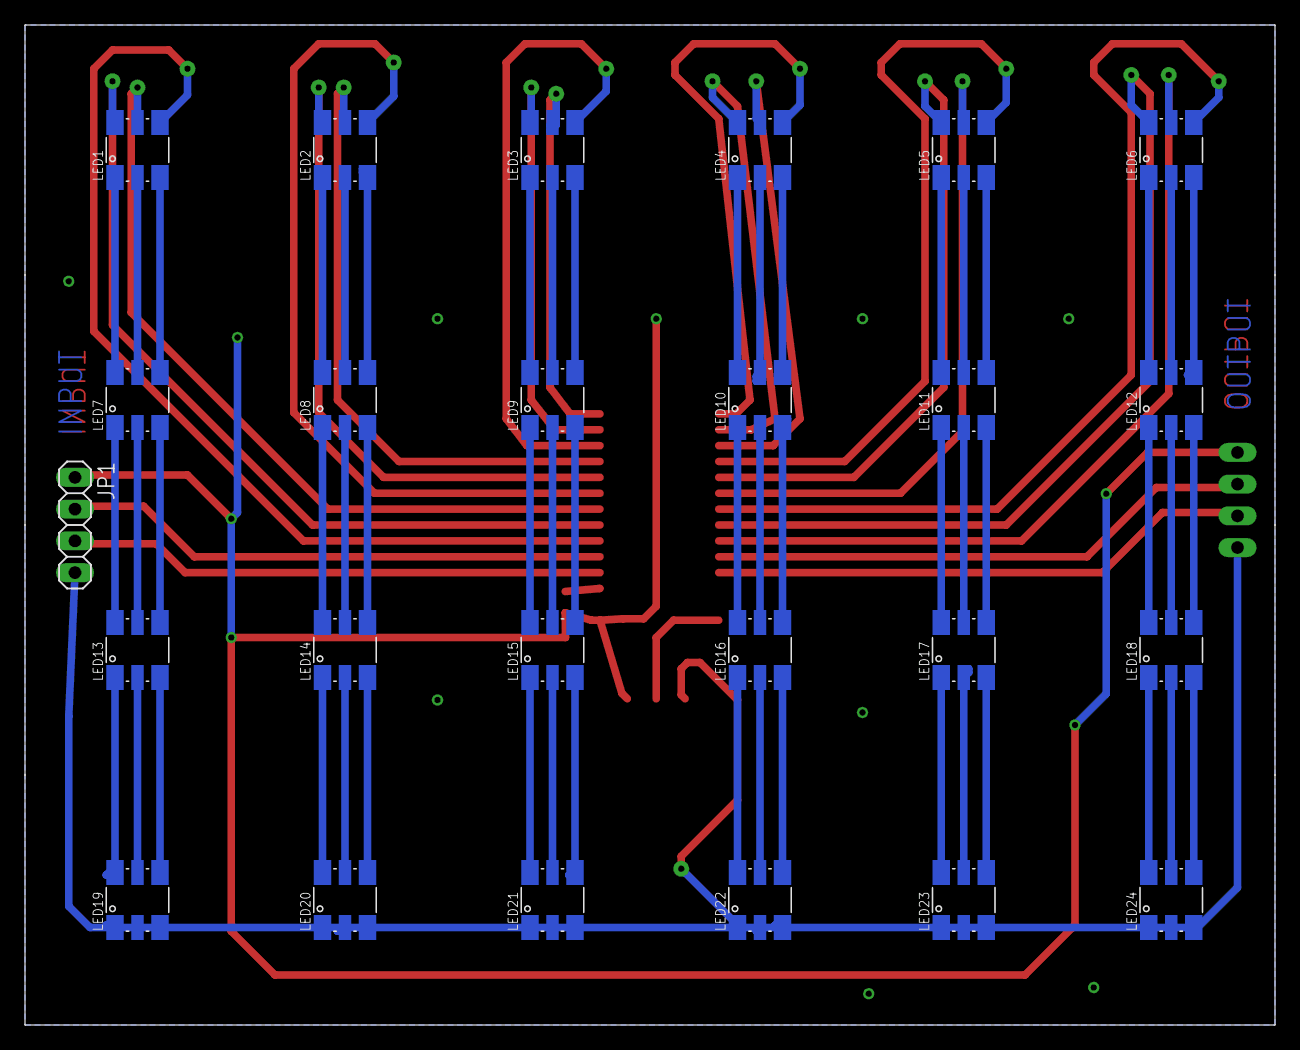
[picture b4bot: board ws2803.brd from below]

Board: 2 copper layers, 100.0 x 80.0 mm, 29 parts (25 on the bottom side), 80 nets.
